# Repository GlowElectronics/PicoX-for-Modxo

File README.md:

# PicoX
PicoX is an interface between the Pi Pico and the original Xbox LPC header

Designed specifically for the Modxo (Modsho) project from shalxmva (https://github.com/shalxmva/modxo)

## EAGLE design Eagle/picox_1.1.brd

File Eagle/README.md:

# PicoX-for-Modxo

 Created in Eagle 6.5

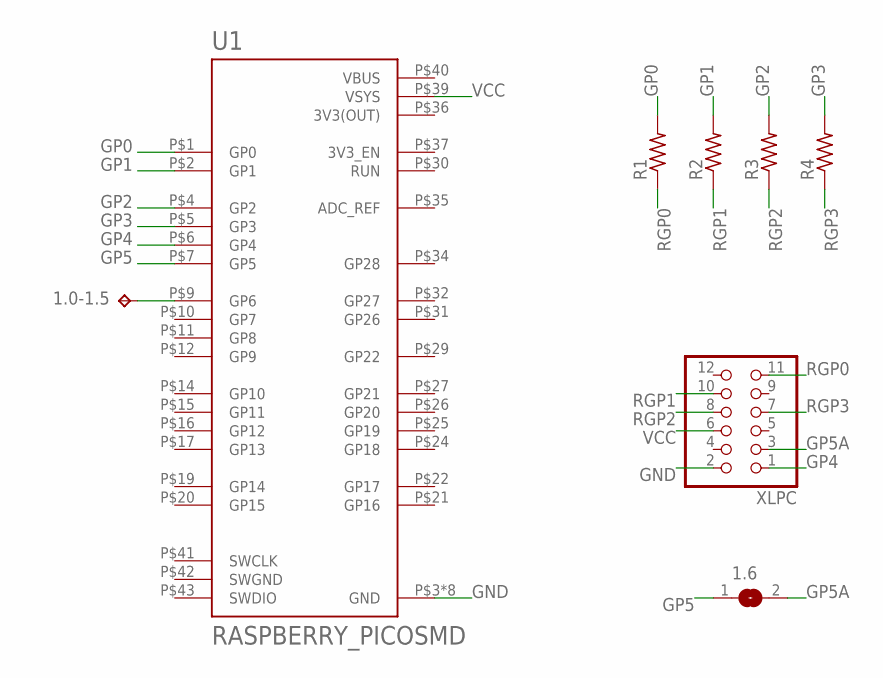
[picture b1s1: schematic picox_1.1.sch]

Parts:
1.0-1.5: TPTP16SQ; TP16SQ
1.6: SJ
R1, R2, R3, R4: R-US_R0805; R0805
U1: RASPBERRY_PICOSMD; PICO-PKG-SMD
XLPC: PINHD-2X6; 2X06

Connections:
3V3(OUT): U1.P$36 (3V3(OUT))
D0: 1.0-1.5.TP, U1.P$9 (GP6)
GND: U1.P$3 (GND), U1.P$8 (GND), U1.P$13 (GND), U1.P$18 (GND), U1.P$23 (GND), U1.P$28 (GND), U1.P$33 (GND), U1.P$38 (GND), XLPC.2
GP0: R1.2, U1.P$1 (GP0)
GP1: R2.2, U1.P$2 (GP1)
GP2: R3.2, U1.P$4 (GP2)
GP3: R4.2, U1.P$5 (GP3)
GP4: U1.P$6 (GP4), XLPC.1
GP5: 1.6.1, U1.P$7 (GP5)
GP5A: 1.6.2, XLPC.3
RGP0: R1.1, XLPC.11
RGP1: R2.1, XLPC.10
RGP2: R3.1, XLPC.8
RGP3: R4.1, XLPC.7
SWGND: U1.P$42 (SWGND)
VBUS: U1.P$40 (VBUS)
VCC: U1.P$39 (VSYS), XLPC.6

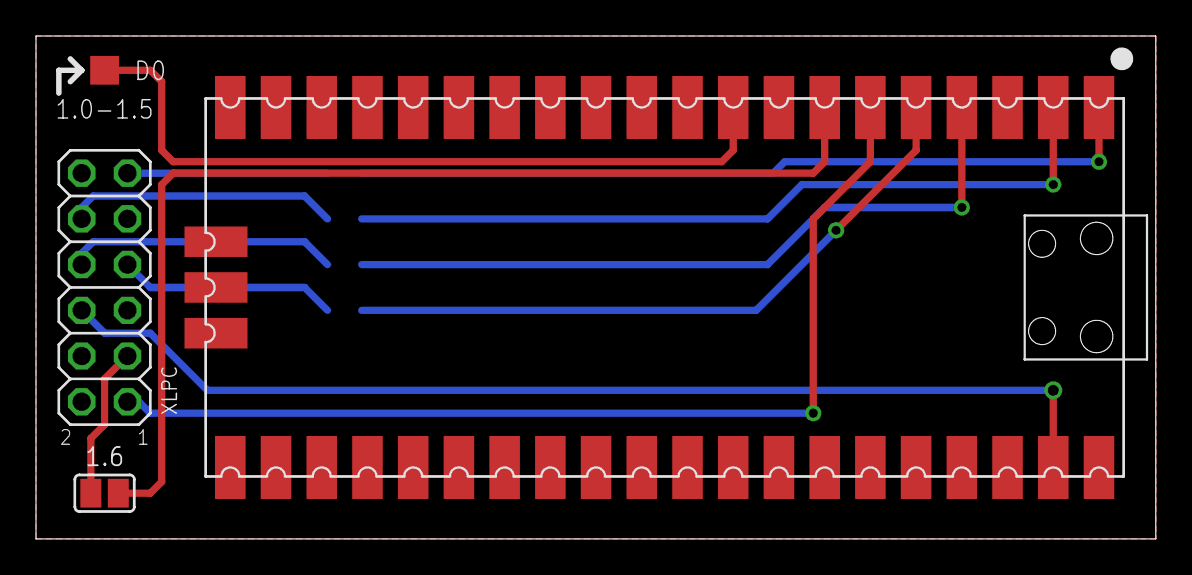
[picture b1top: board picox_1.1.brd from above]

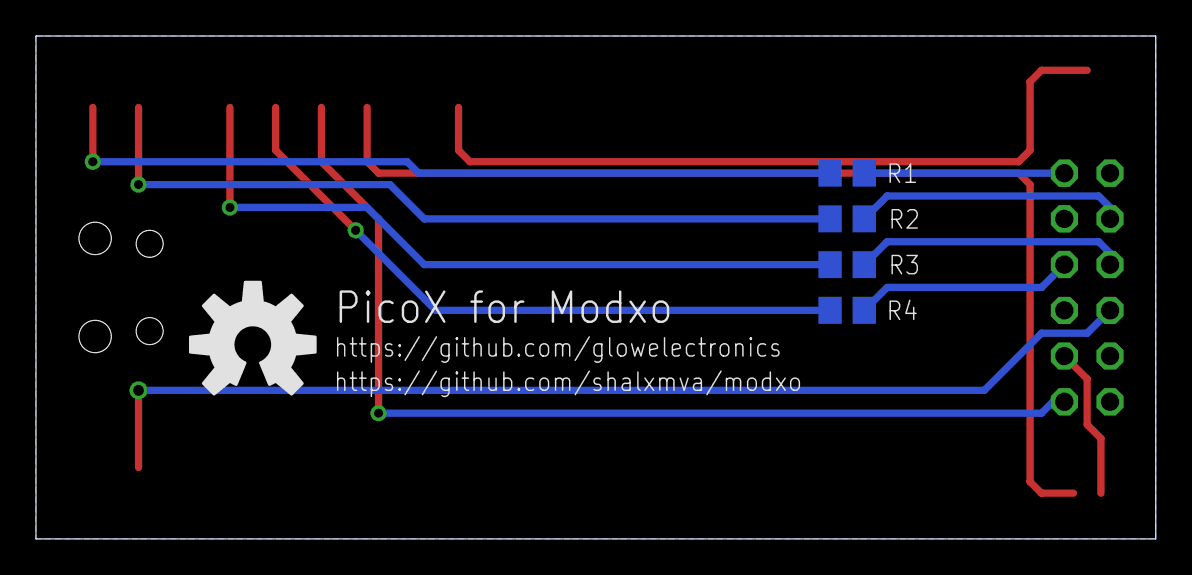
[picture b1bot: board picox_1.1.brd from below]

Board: 2 copper layers, 62.2 x 27.9 mm, 9 parts (5 on the bottom side), 14 nets.

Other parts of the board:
U$5: OSHW-LOGO-L

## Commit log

2024-05-18 Version 1.1

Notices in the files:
parts and their libraries:
SparkFun-Aesthetics: Licensing: Creative Commons ShareAlike 4.0 International - https://creativecommons.org/licenses/by-sa/4.0
